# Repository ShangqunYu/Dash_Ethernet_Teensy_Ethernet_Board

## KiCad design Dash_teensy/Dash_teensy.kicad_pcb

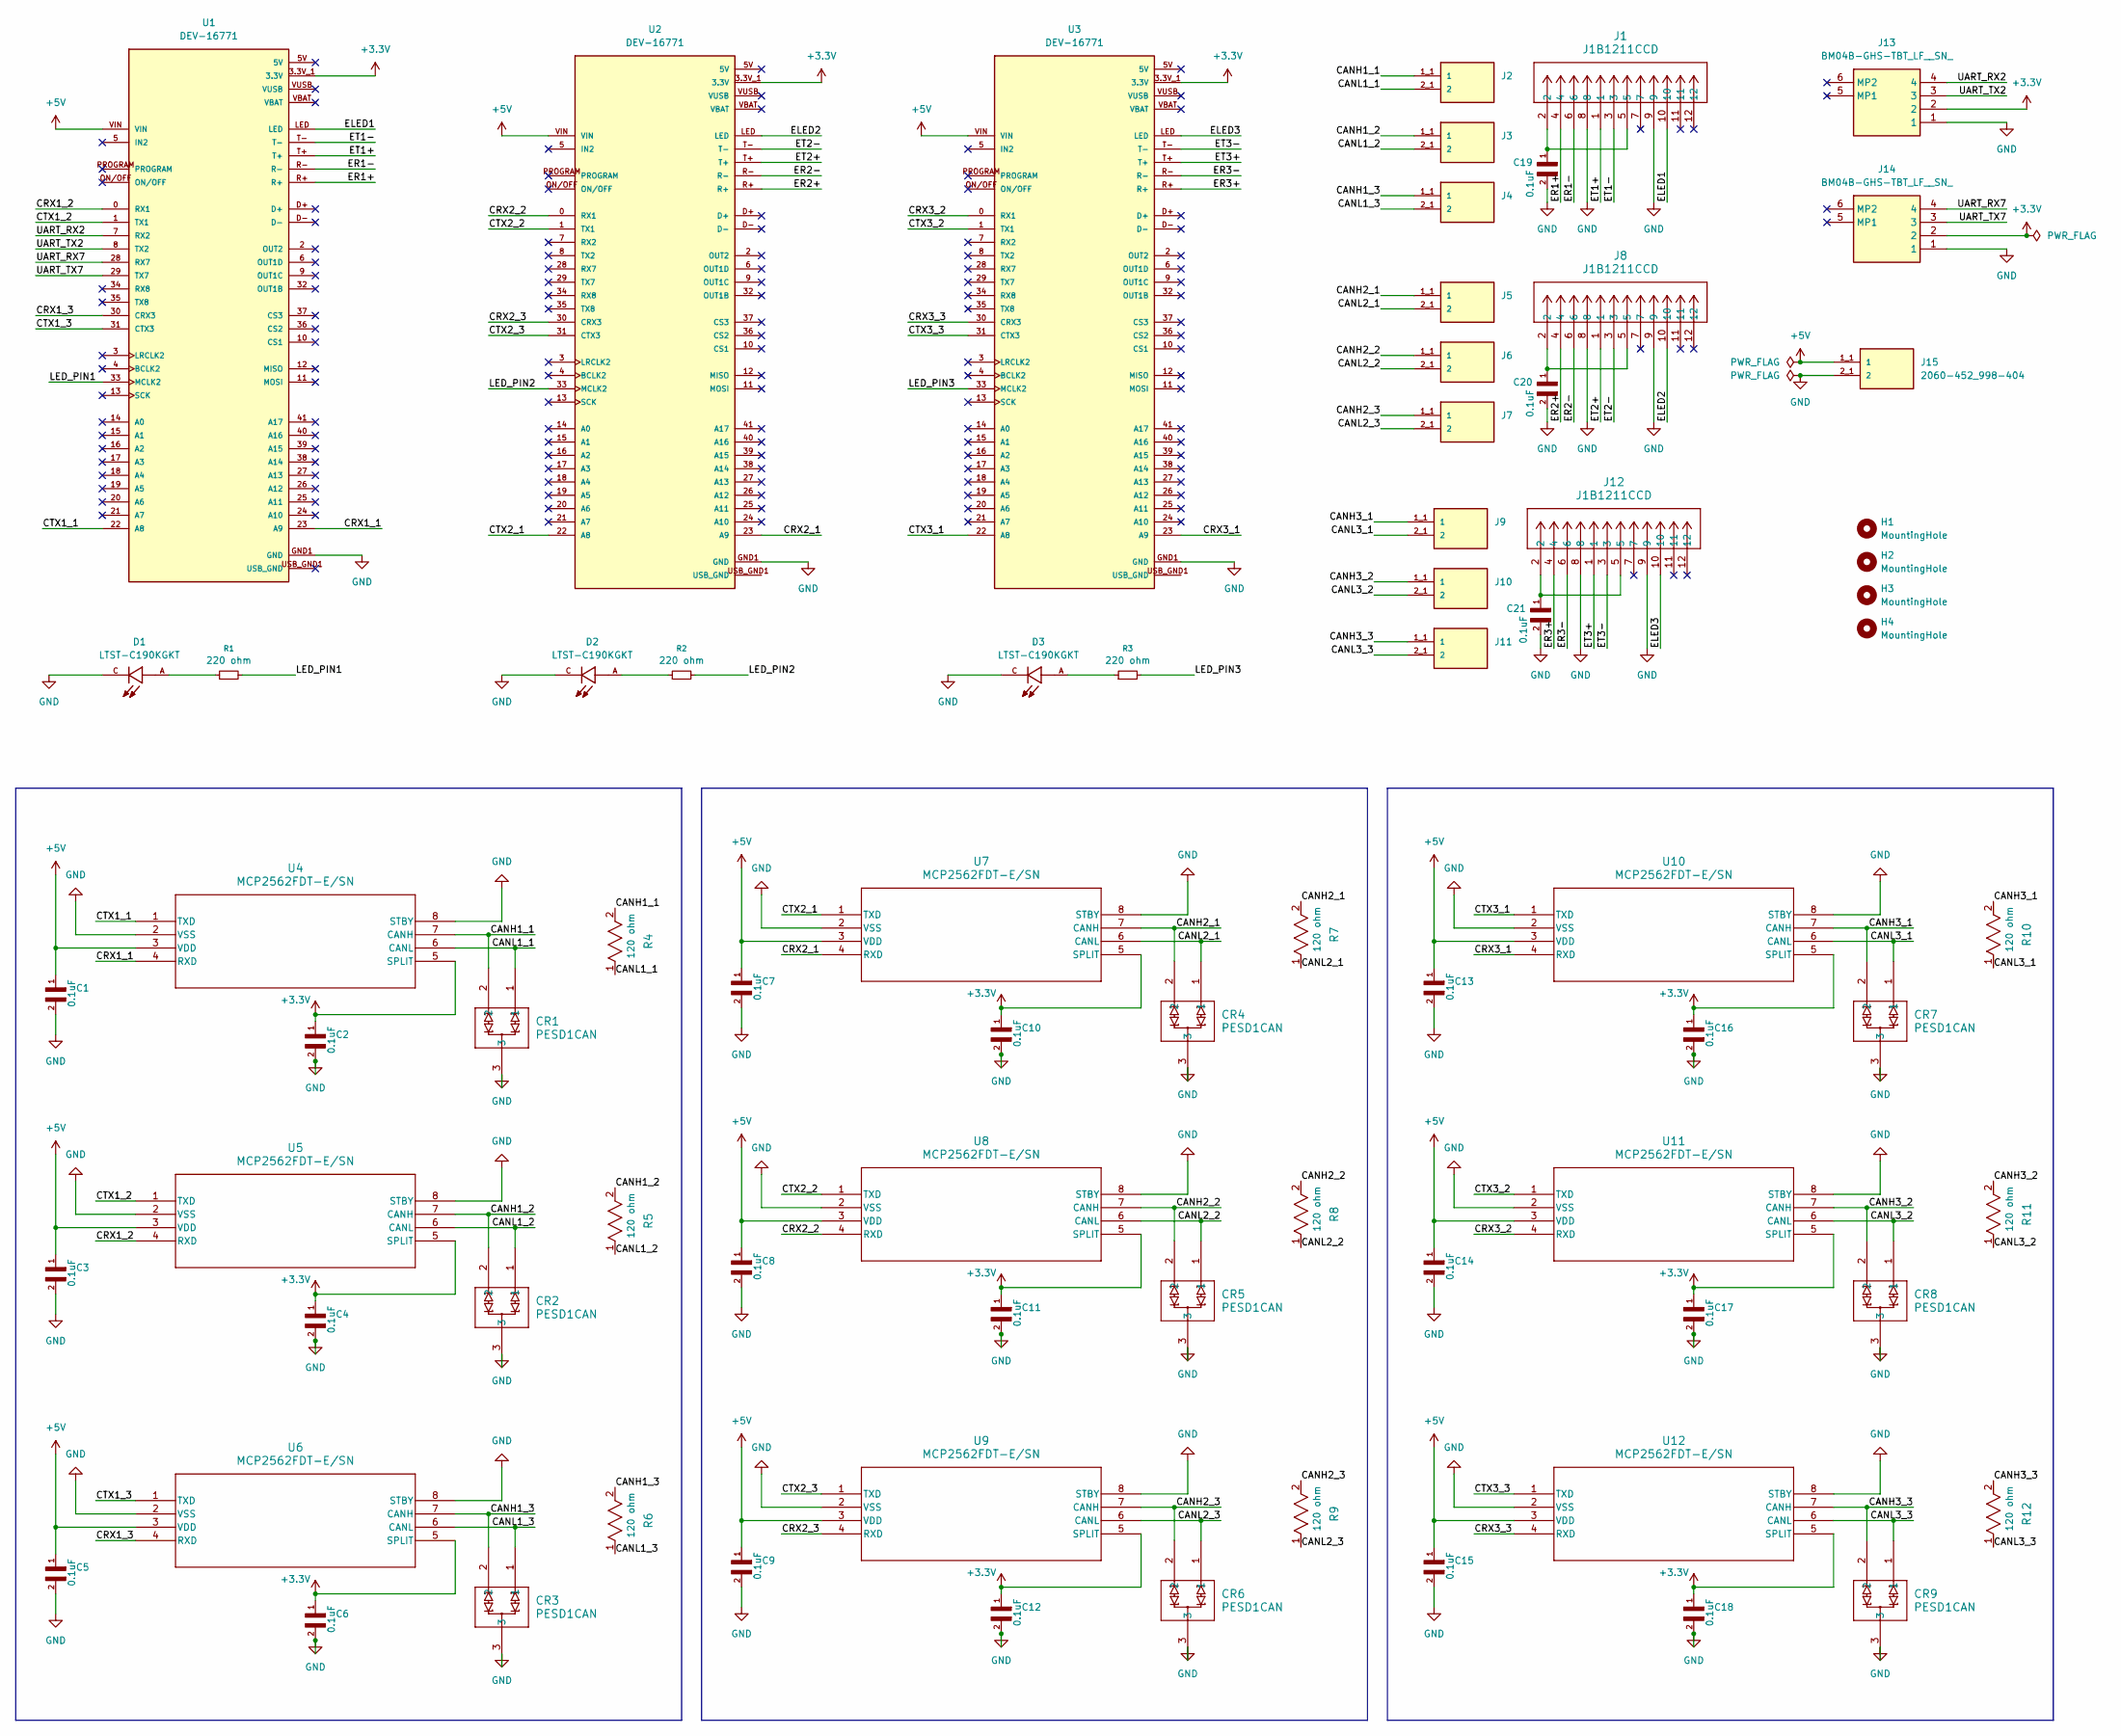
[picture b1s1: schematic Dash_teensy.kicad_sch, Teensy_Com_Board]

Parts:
C1, C2, C3, C4, C5, C6, C7, C8, C9, C10, C11, C12, C13, C14, C15, C16, C17, C18, C19, C20, C21: CL10B104KC8NNNC; CAPC1608X90N
CR1, CR2, CR3, CR4, CR5, CR6, CR7, CR8, CR9: PESD1CAN; SOT23_PESD1_NEX
D1, D2, D3: LTST-C190KGKT; LEDC1608X35N
H1, H2, H3, H4: MountingHole; MountingHole_3.2mm_M3_DIN965_Pad
J1, J8, J12: J1B1211CCD; CONN12_J1B1211CCD_WIZ
J2, J3, J4, J5, J6, J7, J9, J10, J11, J15: 2060-452_998-404; PARTREV N/A
J13, J14: BM04B-GHS-TBT_LF__SN_; BM04BGHSTBTLFSN; Mouser Part Number 306-BM04BGHSTBTLFSNN
R1, R2, R3: RC0603JR-07220RL; RC0603N_PAN
R4, R5, R6, R7, R8, R9, R10, R11, R12: ERA-3AEB121V; RC0603N_PAN
U1, U2, U3: DEV-16771; MODULE_DEV-16771; PARTREV 4.1
U4, U5, U6, U7, U8, U9, U10, U11, U12: MCP2562FDT-E/SN; MCP2562FDT_E_SN

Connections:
+3.3V: C2.1, C4.1, C6.1, C10.1, C11.1, C12.1, C16.1, C17.1, C18.1, J13.2, J14.2, U1.3.3V_1 (3.3V), U1.3.3V_2 (3.3V), U1.3.3V_3 (3.3V), U2.3.3V_1 (3.3V), U2.3.3V_2 (3.3V), U2.3.3V_3 (3.3V), U3.3.3V_1 (3.3V), U3.3.3V_2 (3.3V), U3.3.3V_3 (3.3V), U4.5 (SPLIT), U5.5 (SPLIT), U6.5 (SPLIT), U7.5 (SPLIT), U8.5 (SPLIT), U9.5 (SPLIT), U10.5 (SPLIT), U11.5 (SPLIT), U12.5 (SPLIT)
+5V: C1.1, C3.1, C5.1, C7.1, C8.1, C9.1, C13.1, C14.1, C15.1, J15.1_1 (1), U1.VIN, U2.VIN, U3.VIN, U4.3 (VDD), U5.3 (VDD), U6.3 (VDD), U7.3 (VDD), U8.3 (VDD), U9.3 (VDD), U10.3 (VDD), U11.3 (VDD), U12.3 (VDD)
/CANH1_1: CR1.2, J2.1_1 (1), R4.2, U4.7 (CANH)
/CANH1_2: CR2.2, J3.1_1 (1), R5.2, U5.7 (CANH)
/CANH1_3: CR3.2, J4.1_1 (1), R6.2, U6.7 (CANH)
/CANH2_1: CR4.2, J5.1_1 (1), R7.2, U7.7 (CANH)
/CANH2_2: CR5.2, J6.1_1 (1), R8.2, U8.7 (CANH)
/CANH2_3: CR6.2, J7.1_1 (1), R9.2, U9.7 (CANH)
/CANH3_1: CR7.2, J9.1_1 (1), R10.2, U10.7 (CANH)
/CANH3_2: CR8.2, J10.1_1 (1), R11.2, U11.7 (CANH)
/CANH3_3: CR9.2, J11.1_1 (1), R12.2, U12.7 (CANH)
/CANL1_1: CR1.1, J2.2_1 (2), R4.1, U4.6 (CANL)
/CANL1_2: CR2.1, J3.2_1 (2), R5.1, U5.6 (CANL)
/CANL1_3: CR3.1, J4.2_1 (2), R6.1, U6.6 (CANL)
/CANL2_1: CR4.1, J5.2_1 (2), R7.1, U7.6 (CANL)
/CANL2_2: CR5.1, J6.2_1 (2), R8.1, U8.6 (CANL)
/CANL2_3: CR6.1, J7.2_1 (2), R9.1, U9.6 (CANL)
/CANL3_1: CR7.1, J9.2_1 (2), R10.1, U10.6 (CANL)
/CANL3_2: CR8.1, J10.2_1 (2), R11.1, U11.6 (CANL)
/CANL3_3: CR9.1, J11.2_1 (2), R12.1, U12.6 (CANL)
/CRX1_1: U1.23 (A9), U4.4 (RXD)
/CRX1_2: U1.0 (RX1), U5.4 (RXD)
/CRX1_3: U1.30 (CRX3), U6.4 (RXD)
/CRX2_1: U2.23 (A9), U7.4 (RXD)
/CRX2_2: U2.0 (RX1), U8.4 (RXD)
/CRX2_3: U2.30 (CRX3), U9.4 (RXD)
/CRX3_1: U3.23 (A9), U10.4 (RXD)
/CRX3_2: U3.0 (RX1), U11.4 (RXD)
/CRX3_3: U3.30 (CRX3), U12.4 (RXD)
/CTX1_1: U1.22 (A8), U4.1 (TXD)
/CTX1_2: U1.1 (TX1), U5.1 (TXD)
/CTX1_3: U1.31 (CTX3), U6.1 (TXD)
/CTX2_1: U2.22 (A8), U7.1 (TXD)
/CTX2_2: U2.1 (TX1), U8.1 (TXD)
/CTX2_3: U2.31 (CTX3), U9.1 (TXD)
/CTX3_1: U3.22 (A8), U10.1 (TXD)
/CTX3_2: U3.1 (TX1), U11.1 (TXD)
/CTX3_3: U3.31 (CTX3), U12.1 (TXD)
/ELED1: J1.10, U1.LED
/ELED2: J8.10, U2.LED
/ELED3: J12.10, U3.LED
/ER1+: J1.4, U1.R+
/ER1-: J1.6, U1.R-
/ER2+: J8.4, U2.R+
/ER2-: J8.6, U2.R-
/ER3+: J12.4, U3.R+
/ER3-: J12.6, U3.R-
/ET1+: J1.1, U1.T+
/ET1-: J1.3, U1.T-
/ET2+: J8.1, U2.T+
/ET2-: J8.3, U2.T-
/ET3+: J12.1, U3.T+
/ET3-: J12.3, U3.T-
/LED_PIN1: R1.2, U1.33 (MCLK2)
/LED_PIN2: R2.2, U2.33 (MCLK2)
/LED_PIN3: R3.2, U3.33 (MCLK2)
/UART_RX2: J13.4, U1.7 (RX2)
/UART_RX7: J14.4, U1.28 (RX7)
/UART_TX2: J13.3, U1.8 (TX2)
/UART_TX7: J14.3, U1.29 (TX7)
GND: C1.2, C2.2, C3.2, C4.2, C5.2, C6.2, C7.2, C8.2, C9.2, C10.2, C11.2, C12.2, C13.2, C14.2, C15.2, C16.2, C17.2, C18.2, C19.2, C20.2, C21.2, CR1.3, CR2.3, CR3.3, CR4.3, CR5.3, CR6.3, CR7.3, CR8.3, CR9.3, D1.C, D2.C, D3.C, J1.8, J1.9, J8.8, J8.9, J12.8, J12.9, J13.1, J14.1, J15.2_1 (2), U1.GND1 (GND), U1.GND2 (GND), U1.GND3 (GND), U1.GND4 (GND), U1.GND5 (GND), U2.GND1 (GND), U2.GND2 (GND), U2.GND3 (GND), U2.GND4 (GND), U2.GND5 (GND), U3.GND1 (GND), U3.GND2 (GND), U3.GND3 (GND), U3.GND4 (GND), U3.GND5 (GND), U4.2 (VSS), U4.8 (STBY), U5.2 (VSS), U5.8 (STBY), U6.2 (VSS), U6.8 (STBY), U7.2 (VSS), U7.8 (STBY), U8.2 (VSS), U8.8 (STBY), U9.2 (VSS), U9.8 (STBY), U10.2 (VSS), U10.8 (STBY), U11.2 (VSS), U11.8 (STBY), U12.2 (VSS), U12.8 (STBY)
unnamed: C19.1, J1.2, J1.5
unnamed: C20.1, J8.2, J8.5
unnamed: C21.1, J12.2, J12.5
unnamed: D1.A, R1.1
unnamed: D2.A, R2.1
unnamed: D3.A, R3.1

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
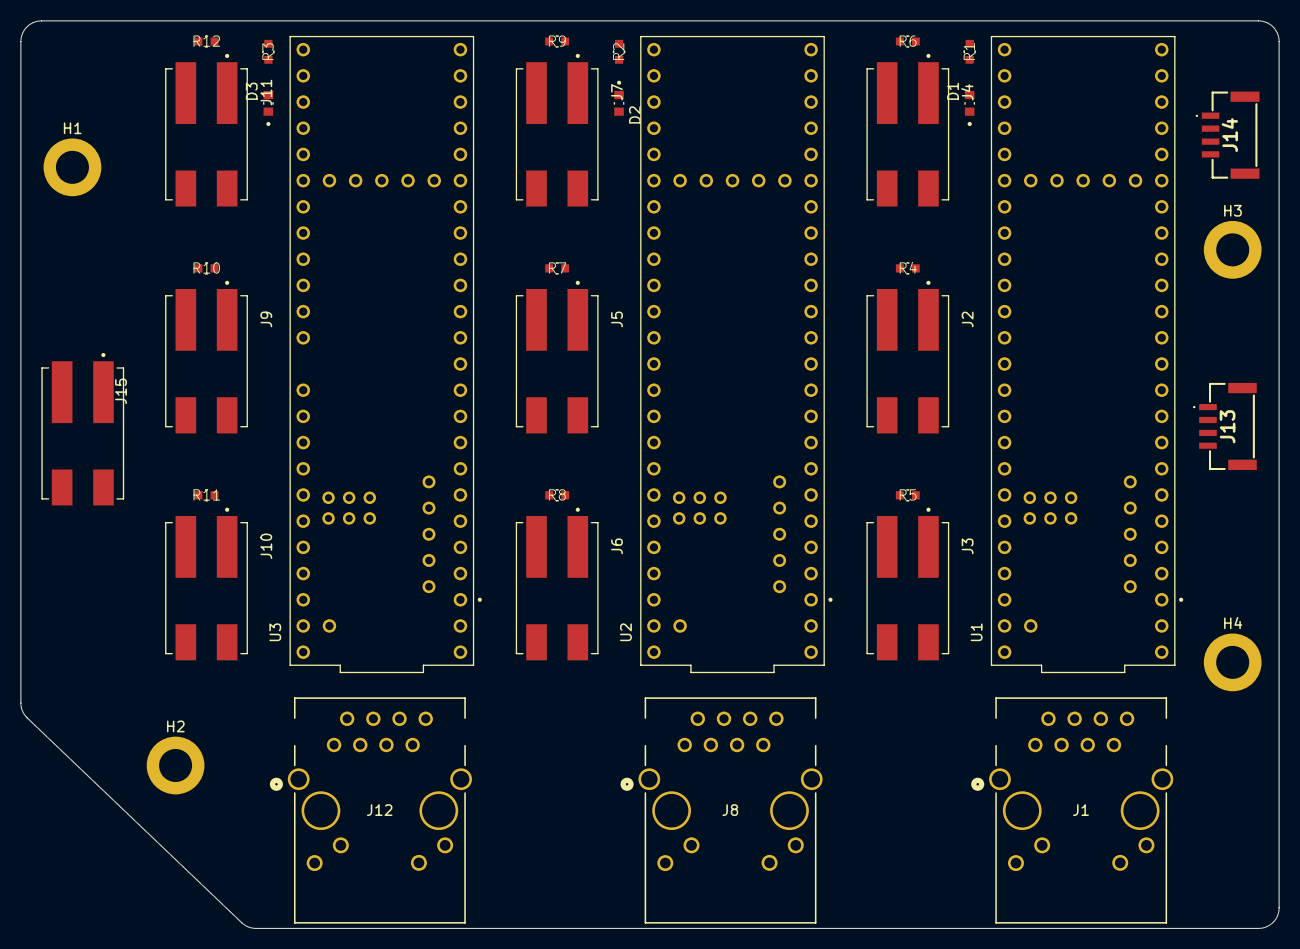
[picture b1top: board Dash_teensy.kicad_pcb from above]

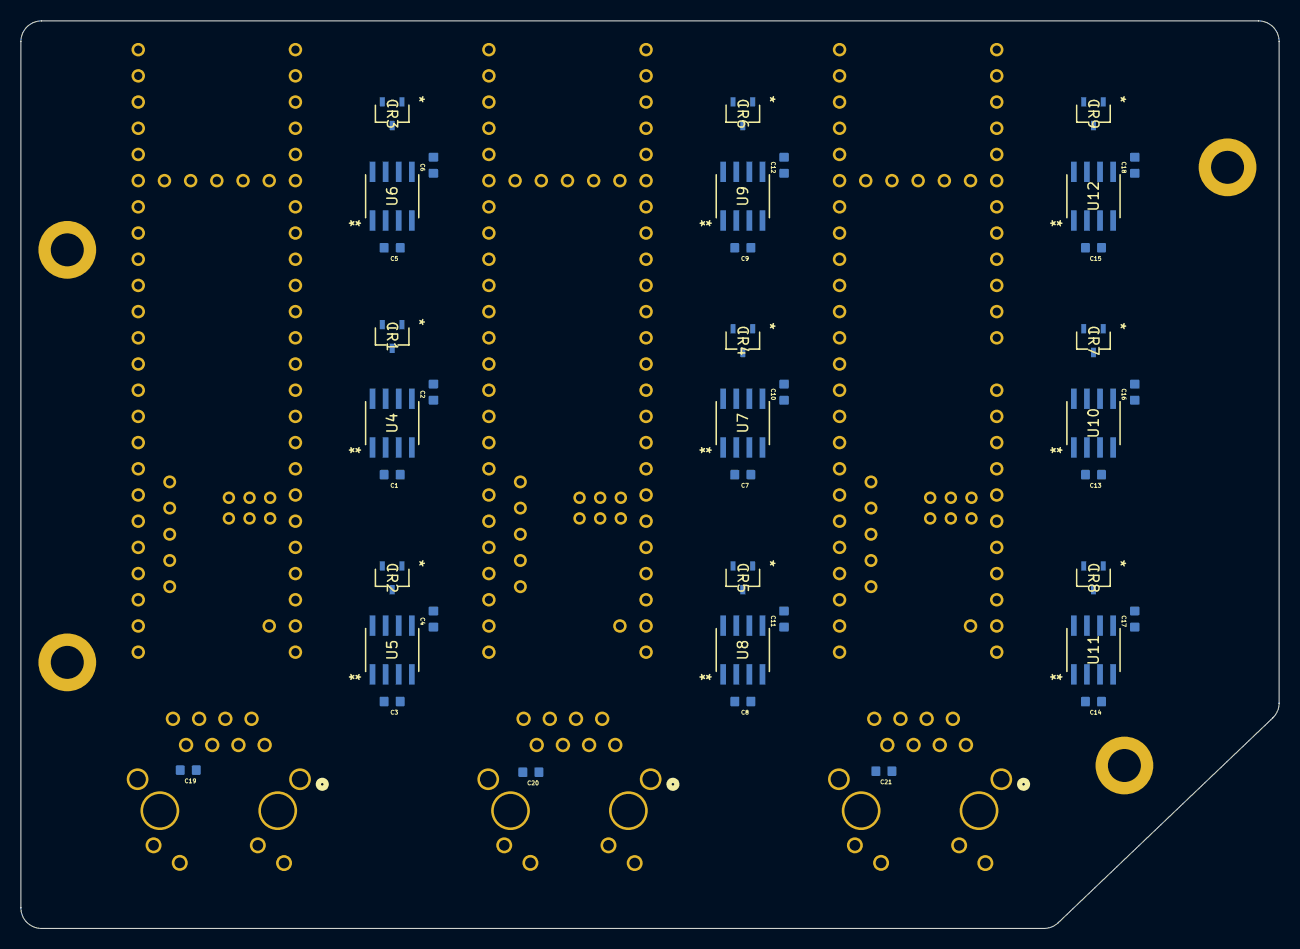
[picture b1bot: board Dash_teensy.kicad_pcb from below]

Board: 2 copper layers, 122.0 x 88.0 mm, 76 parts (39 on the bottom side), 68 nets.

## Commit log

2026-05-28 Create t
2026-05-30 finish schematic
2026-05-30 figured out placement
